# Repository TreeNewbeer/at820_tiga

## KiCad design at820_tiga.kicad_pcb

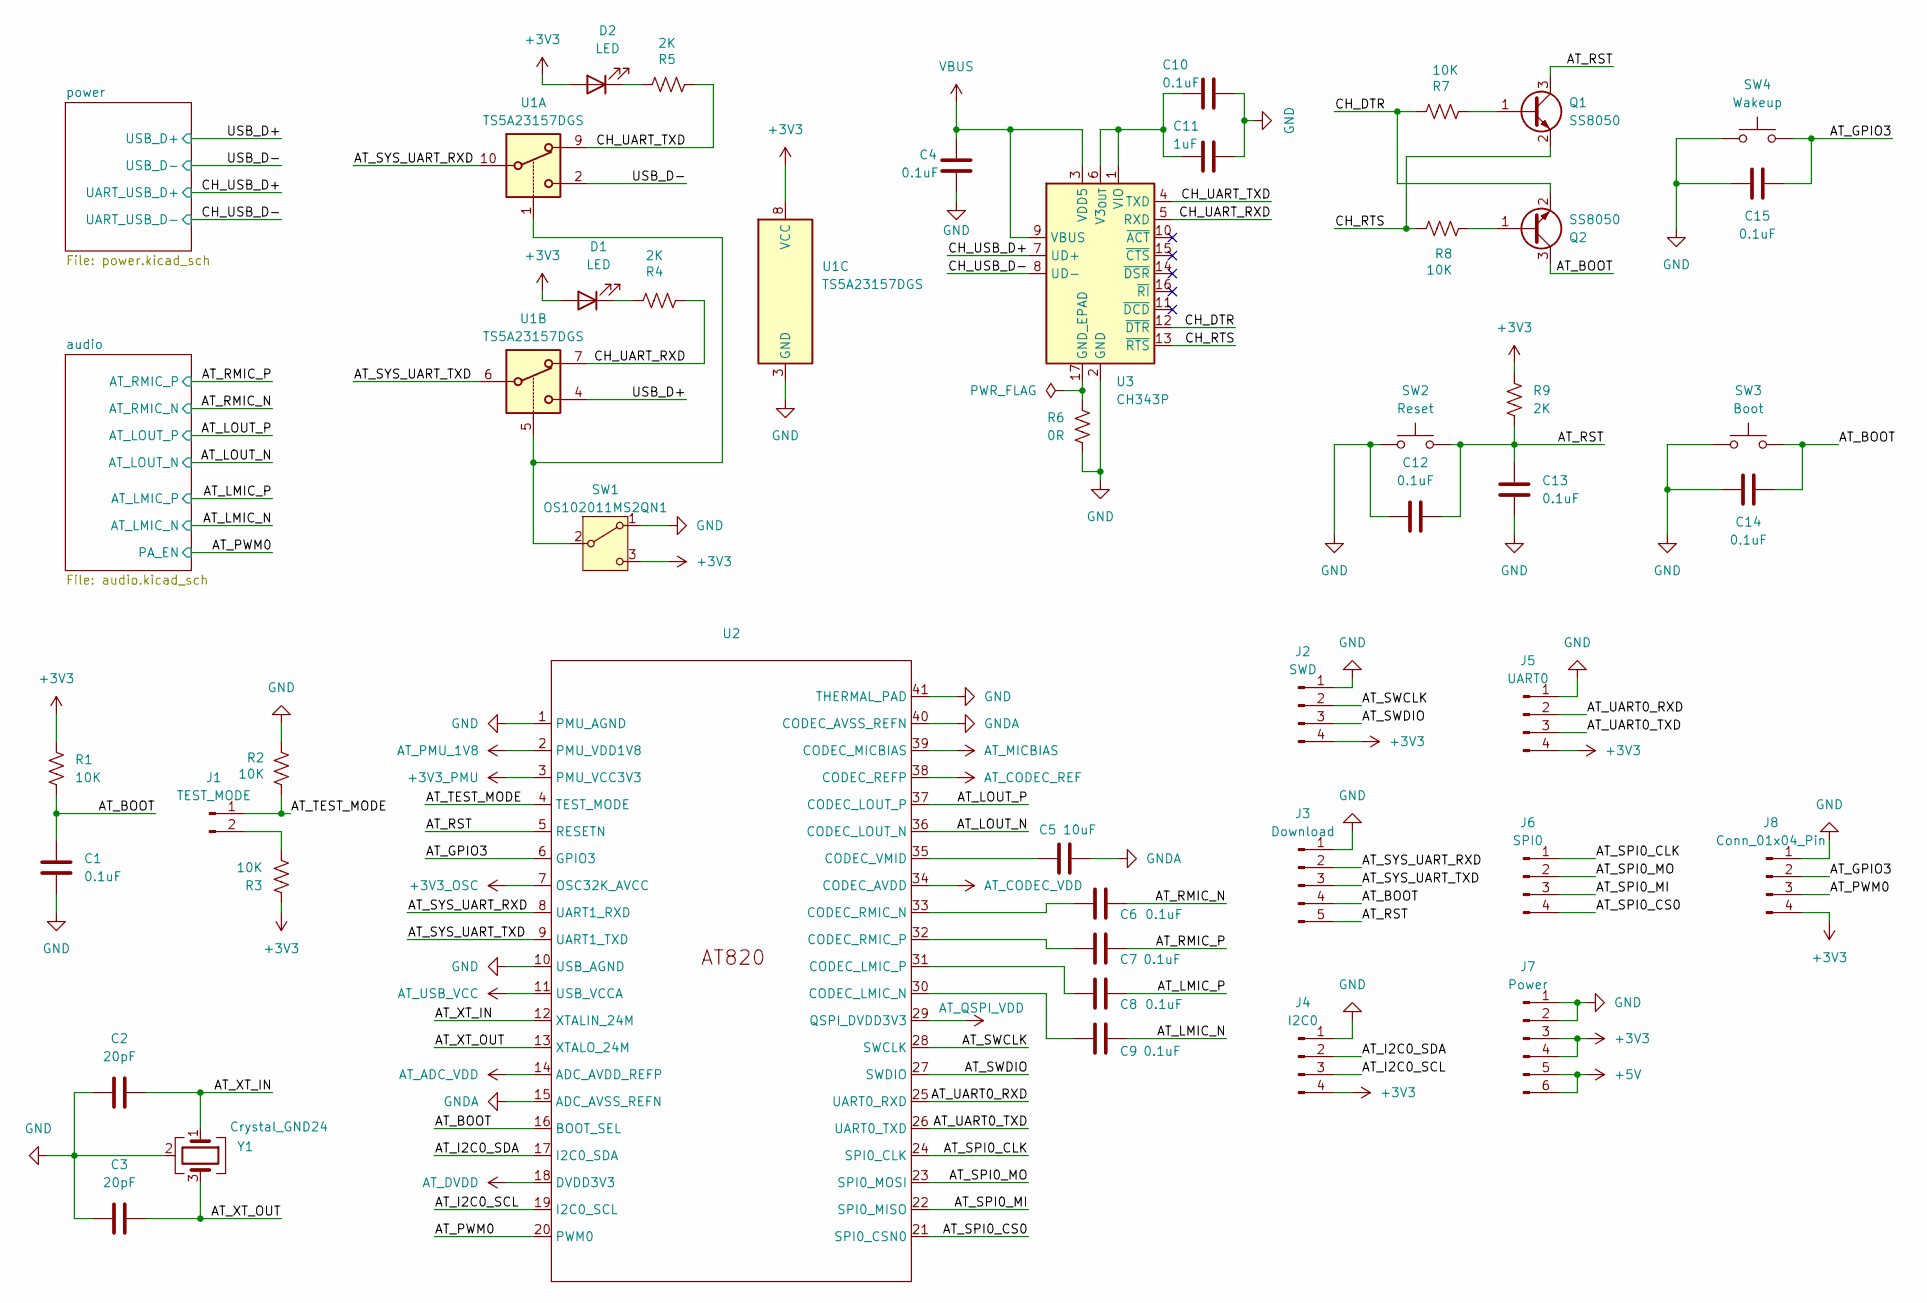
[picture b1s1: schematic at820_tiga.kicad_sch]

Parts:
C1, C4, C6, C7, C8, C9, C10, C12, C13, C14, C15: 0.1uF; C_0603_1608Metric_Pad1.08x0.95mm_HandSolder
C2, C3: 20pF; C_0603_1608Metric_Pad1.08x0.95mm_HandSolder
C5: 10uF; C_0603_1608Metric_Pad1.08x0.95mm_HandSolder
C11: 1uF; C_0603_1608Metric_Pad1.08x0.95mm_HandSolder
D1, D2: LED; LED_0603_1608Metric_Pad1.05x0.95mm_HandSolder
J1: TEST_MODE; PinHeader_1x02_P2.54mm_Vertical
J2: SWD; PinHeader_1x04_P2.54mm_Vertical
J3: Download; PinHeader_1x05_P2.54mm_Vertical
J4: I2C0; PinHeader_1x04_P2.54mm_Vertical
J5: UART0; PinHeader_1x04_P2.54mm_Vertical
J6: SPI0; PinHeader_1x04_P2.54mm_Vertical
J7: Power; PinHeader_1x06_P2.54mm_Vertical
J8: Conn_01x04_Pin; PinHeader_1x04_P2.54mm_Vertical
Q1, Q2: SS8050; SOT-23
R1, R2, R3, R7, R8: 10K; R_0603_1608Metric_Pad0.98x0.95mm_HandSolder
R4, R5, R9: 2K; R_0603_1608Metric_Pad0.98x0.95mm_HandSolder
R6: 0R; R_0603_1608Metric_Pad0.98x0.95mm_HandSolder
SW1: OS102011MS2QN1; SW_Slide_SPDT_Straight_CK_OS102011MS2Q
SW2: Reset; SW_SPST_PTS810
SW3: Boot; SW_SPST_PTS810
SW4: Wakeup; SW_SPST_PTS810
U1: TS5A23157DGS; TSSOP-10_3x3mm_P0.5mm
U2: QFN-40-1EP_5x5mm_P0.4mm_EP3.6x3.6mm
U3: CH343P; WCH_QFN-16-1EP_3x3mm_P0.5mm_EP1.8x1.8mm
Y1: Crystal_GND24; Crystal_SMD_3225-4Pin_3.2x2.5mm

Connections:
+3V3: D1.2 (A), D2.2 (A), J2.4, J4.4, J5.4, J7.3, J7.4, J8.4, R1.1, R3.1, R9.1, SW1.3 (C), U1.8 (VCC), U2.3 (PMU_VCC3V3), U2.7 (OSC32K_AVCC), U2.11 (USB_VCCA), U2.14 (ADC_AVDD_REFP), U2.18 (DVDD3V3), U2.34 (CODEC_AVDD); also elsewhere on the board
+5V: J7.5, J7.6; also elsewhere on the board
/AT_BOOT: C1.1, C14.2, J3.4, Q2.3 (C), R1.2, SW3.2, U2.16 (BOOT_SEL)
/AT_GPIO3: C15.2, J8.2, SW4.2, U2.6 (GPIO3)
/AT_I2C0_SCL: J4.3, U2.19 (I2C0_SCL)
/AT_I2C0_SDA: J4.2, U2.17 (I2C0_SDA)
/AT_LMIC_N: C9.1; also elsewhere on the board
/AT_LMIC_P: C8.1; also elsewhere on the board
/AT_LOUT_N: U2.36 (CODEC_LOUT_N); also elsewhere on the board
/AT_LOUT_P: U2.37 (CODEC_LOUT_P); also elsewhere on the board
/AT_PWM0: J8.3, U2.20 (PWM0); also elsewhere on the board
/AT_RMIC_N: C6.1; also elsewhere on the board
/AT_RMIC_P: C7.1; also elsewhere on the board
/AT_RST: C12.2, C13.1, J3.5, Q1.3 (C), R9.2, SW2.2, U2.5 (RESETN)
/AT_SPI0_CLK: J6.1, U2.24 (SPI0_CLK)
/AT_SPI0_CS0: J6.4, U2.21 (SPI0_CSN0)
/AT_SPI0_MI: J6.3, U2.22 (SPI0_MISO)
/AT_SPI0_MO: J6.2, U2.23 (SPI0_MOSI)
/AT_SWCLK: J2.2, U2.28 (SWCLK)
/AT_SWDIO: J2.3, U2.27 (SWDIO)
/AT_SYS_UART_RXD: J3.2, U1.10, U2.8 (UART1_RXD)
/AT_SYS_UART_TXD: J3.3, U1.6, U2.9 (UART1_TXD)
/AT_TEST_MODE: J1.1, R2.1, U2.4 (TEST_MODE)
/AT_UART0_RXD: J5.2, U2.25 (UART0_RXD)
/AT_UART0_TXD: J5.3, U2.26 (UART0_TXD)
/AT_XT_IN: C2.1, U2.12 (XTALIN_24M), Y1.1
/AT_XT_OUT: C3.1, U2.13 (XTALO_24M), Y1.3
/CH_DTR: Q2.2 (E), R7.2, U3.12 (~DTR)
/CH_RTS: Q1.2 (E), R8.1, U3.13 (~RTS)
/CH_UART_RXD: R4.1, U1.7, U3.5 (RXD)
/CH_UART_TXD: R5.1, U1.9, U3.4 (TXD)
/CH_USB_D+: U3.7 (UD+); also elsewhere on the board
/CH_USB_D-: U3.8 (UD-); also elsewhere on the board
/USB_D+: U1.4; also elsewhere on the board
/USB_D-: U1.2; also elsewhere on the board
AT_CODEC_REF: U2.38 (CODEC_REFP); also elsewhere on the board
AT_MICBIAS: U2.39 (CODEC_MICBIAS); also elsewhere on the board
AT_PMU_1V8: U2.2 (PMU_VDD1V8); also elsewhere on the board
AT_QSPI_VDD: U2.29 (QSPI_DVDD3V3); also elsewhere on the board
GND: C1.2, C2.2, C3.2, C4.2, C10.2, C11.2, C12.1, C13.2, C14.1, C15.1, J2.1, J3.1, J4.1, J5.1, J7.1, J7.2, J8.1, R2.2, R6.1, SW1.1 (A), SW2.1, SW3.1, SW4.1, U1.3 (GND), U2.1 (PMU_AGND), U2.10 (USB_AGND), U2.41 (THERMAL_PAD), U3.2 (GND), Y1.2 (G), Y1.4 (G); also elsewhere on the board
GNDA: C5.1, U2.15 (ADC_AVSS_REFN), U2.40 (CODEC_AVSS_REFN); also elsewhere on the board
unnamed: D1.1 (K), R4.2
unnamed: D2.1 (K), R5.2
unnamed: J1.2, R3.2
unnamed: Q1.1 (B), R7.1
unnamed: Q2.1 (B), R8.2
unnamed: SW1.2 (B), U1.1, U1.5
unnamed: C9.2, U2.30 (CODEC_LMIC_N)
unnamed: C8.2, U2.31 (CODEC_LMIC_P)
unnamed: C6.2, U2.33 (CODEC_RMIC_N)
unnamed: C7.2, U2.32 (CODEC_RMIC_P)
unnamed: C5.2, U2.35 (CODEC_VMID)
unnamed: R6.2, U3.17 (GND_EPAD)
unnamed: C10.1, C11.1, U3.1 (VIO), U3.6 (V3_{OUT})
VBUS: C4.1, U3.3 (VDD5), U3.9 (VBUS); also elsewhere on the board

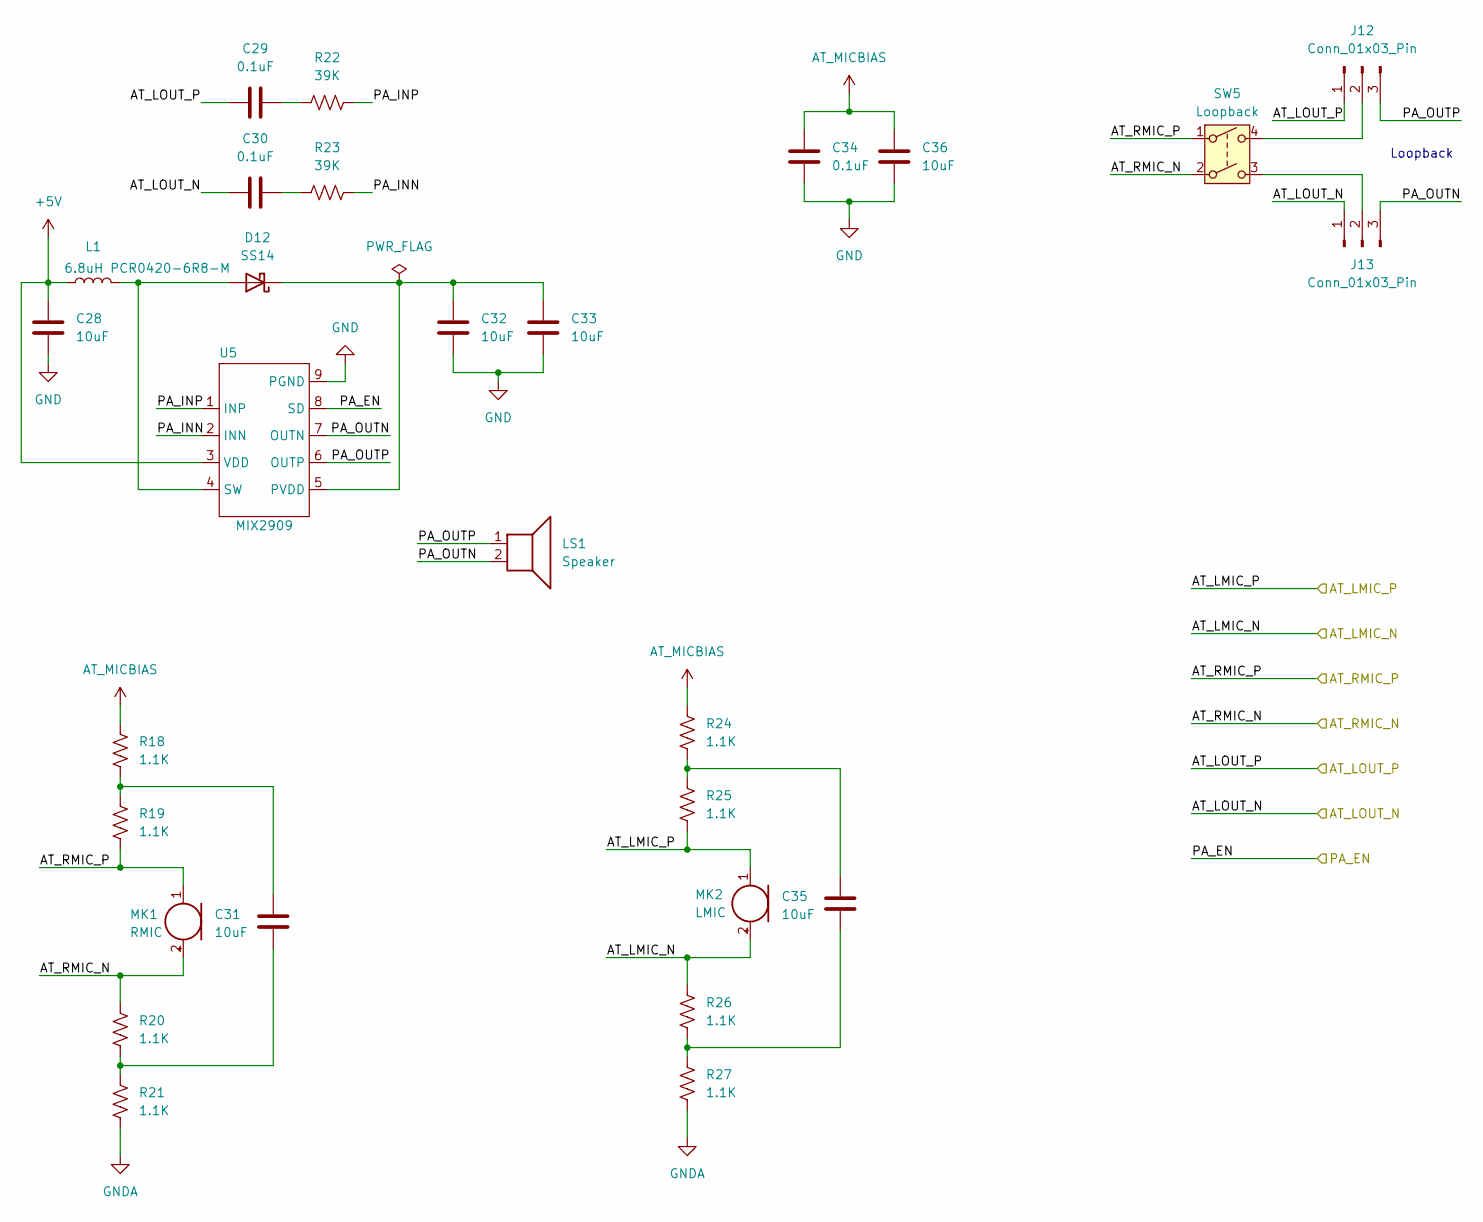
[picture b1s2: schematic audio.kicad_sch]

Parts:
C28, C31, C32, C33, C35, C36: 10uF; C_0603_1608Metric_Pad1.08x0.95mm_HandSolder
C29, C30, C34: 0.1uF; C_0603_1608Metric_Pad1.08x0.95mm_HandSolder
D12: SS14; D_SMA_Handsoldering
J12, J13: Conn_01x03_Pin; PinHeader_1x03_P2.54mm_Vertical
L1: 6.8uH PCR0420-6R8-M; L_APV_APH0420
LS1: Speaker; Molex_PicoBlade_53047-0210_1x02_P1.25mm_Vertical
MK1: RMIC; POM-2244P-C3310-2-R
MK2: LMIC; POM-2244P-C3310-2-R
R18, R19, R20, R21, R24, R25, R26, R27: 1.1K; R_0603_1608Metric_Pad0.98x0.95mm_HandSolder
R22, R23: 39K; R_0603_1608Metric_Pad0.98x0.95mm_HandSolder
SW5: Loopback; SW_DIP_SPSTx02_Slide_Copal_CHS-02B_W7.62mm_P1.27mm
U5: MIX2909; SOIC-8-1EP_3.9x4.9mm_P1.27mm_EP2.29x3mm

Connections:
+5V: C28.1, L1.1, U5.3 (VDD); also elsewhere on the board
/AT_LMIC_N: MK2.2 (+), R26.1; also elsewhere on the board
/AT_LMIC_P: MK2.1 (-), R25.2; also elsewhere on the board
/AT_LOUT_N: C30.1, J13.1; also elsewhere on the board
/AT_LOUT_P: C29.1, J12.1; also elsewhere on the board
/AT_PWM0: U5.8 (SD); also elsewhere on the board
/AT_RMIC_N: MK1.2 (+), R20.1, SW5.2; also elsewhere on the board
/AT_RMIC_P: MK1.1 (-), R19.2, SW5.1; also elsewhere on the board
/audio/PA_INN: R23.2, U5.2 (INN)
/audio/PA_INP: R22.2, U5.1 (INP)
/audio/PA_OUTN: J13.3, LS1.2, U5.7 (OUTN)
/audio/PA_OUTP: J12.3, LS1.1, U5.6 (OUTP)
AT_MICBIAS: C34.1, C36.1, R18.1, R24.1; also elsewhere on the board
GND: C28.2, C32.2, C33.2, C34.2, C36.2, U5.9 (PGND); also elsewhere on the board
GNDA: R21.2, R27.2; also elsewhere on the board
unnamed: C29.2, R22.1
unnamed: C30.2, R23.1
unnamed: C31.1, R20.2, R21.1
unnamed: C31.2, R18.2, R19.1
unnamed: C35.1, R26.2, R27.1
unnamed: C35.2, R24.2, R25.1
unnamed: D12.2 (A), L1.2, U5.4 (SW)
unnamed: C32.1, C33.1, D12.1 (K), U5.5 (PVDD)
unnamed: J12.2, SW5.4
unnamed: J13.2, SW5.3

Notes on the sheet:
Loopback

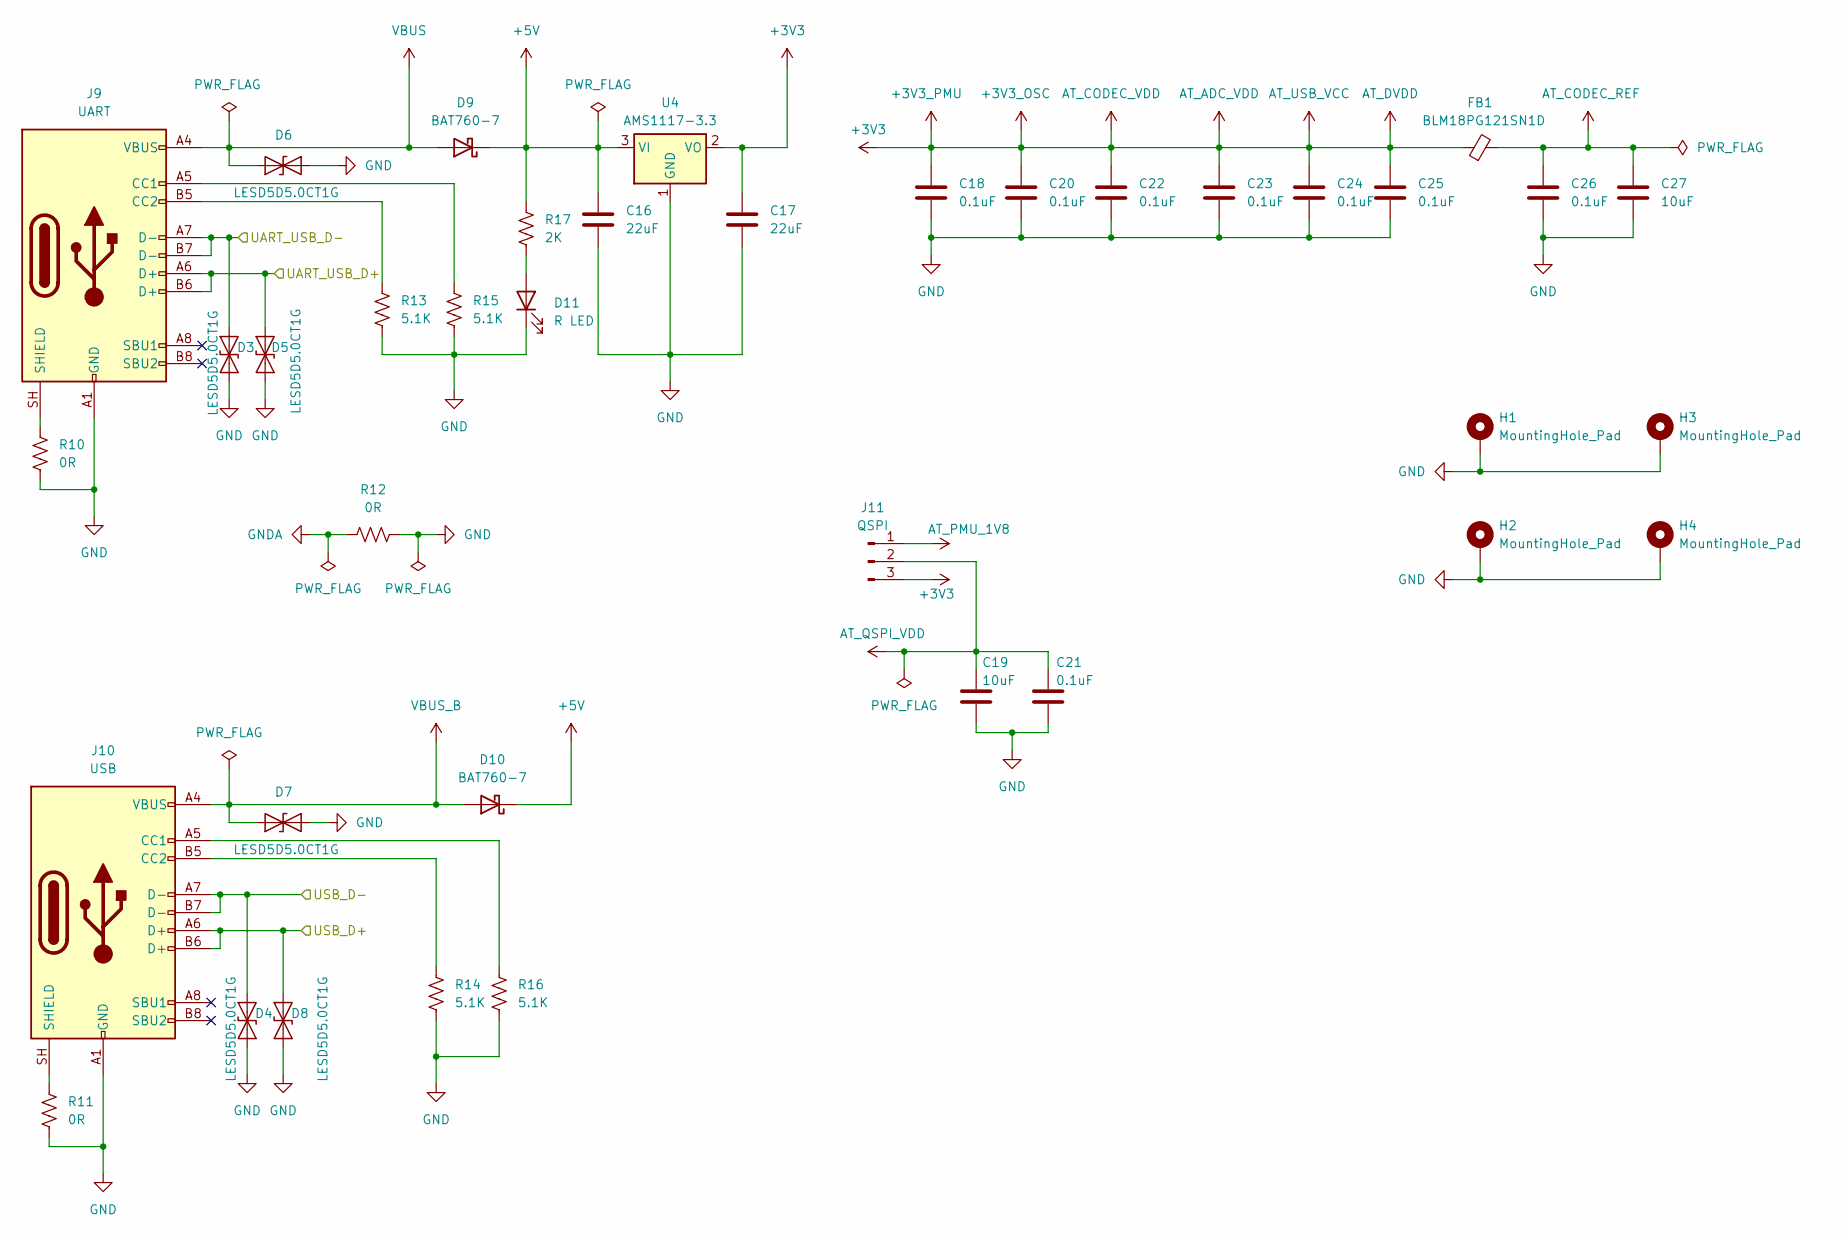
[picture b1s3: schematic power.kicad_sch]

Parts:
C16, C17: 22uF; C_0603_1608Metric_Pad1.08x0.95mm_HandSolder
C18, C20, C21, C22, C23, C24, C25, C26: 0.1uF; C_0603_1608Metric_Pad1.08x0.95mm_HandSolder
C19, C27: 10uF; C_0603_1608Metric_Pad1.08x0.95mm_HandSolder
D3, D4, D5, D6, D7, D8: LESD5D5.0CT1G; D_SOD-523
D9, D10: BAT760-7; D_SOD-323
D11: R LED; LED_0603_1608Metric_Pad1.05x0.95mm_HandSolder
FB1: BLM18PG121SN1D; L_0603_1608Metric_Pad1.05x0.95mm_HandSolder
H1, H2, H3, H4: MountingHole_Pad; MountingHole_3.2mm_M3_Pad
J9: UART; USB_C_Receptacle_GCT_USB4105-xx-A_16P_TopMnt_Horizontal
J10: USB; USB_C_Receptacle_GCT_USB4105-xx-A_16P_TopMnt_Horizontal
J11: QSPI; PinHeader_1x03_P2.54mm_Vertical
R10, R11, R12: 0R; R_0603_1608Metric_Pad0.98x0.95mm_HandSolder
R13, R14, R15, R16: 5.1K; R_0603_1608Metric_Pad0.98x0.95mm_HandSolder
R17: 2K; R_0603_1608Metric_Pad0.98x0.95mm_HandSolder
U4: AMS1117-3.3; SOT-223-3_TabPin2

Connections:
+3V3: C17.1, C18.1, C20.1, C22.1, C23.1, C24.1, C25.1, FB1.1, J11.3, U4.2 (VO); also elsewhere on the board
+5V: C16.1, D9.1 (K), D10.1 (K), R17.1, U4.3 (VI); also elsewhere on the board
/CH_USB_D+: D5.2 (A2), J9.A6 (D+), J9.B6 (D+); also elsewhere on the board
/CH_USB_D-: D3.2 (A2), J9.A7 (D-), J9.B7 (D-); also elsewhere on the board
/USB_D+: D8.2 (A2), J10.A6 (D+), J10.B6 (D+); also elsewhere on the board
/USB_D-: D4.2 (A2), J10.A7 (D-), J10.B7 (D-); also elsewhere on the board
AT_CODEC_REF: C26.1, C27.1, FB1.2; also elsewhere on the board
AT_PMU_1V8: J11.1; also elsewhere on the board
AT_QSPI_VDD: C19.1, C21.1, J11.2; also elsewhere on the board
GND: C16.2, C17.2, C18.2, C19.2, C20.2, C21.2, C22.2, C23.2, C24.2, C25.2, C26.2, C27.2, D3.1 (A1), D4.1 (A1), D5.1 (A1), D6.1 (A1), D7.1 (A1), D8.1 (A1), D11.1 (K), H1.1 (1_1), H2.1 (1_1), H3.1 (1_1), H4.1 (1_1), J9.A1 (GND), J9.A12 (GND), J9.B1 (GND), J9.B12 (GND), J10.A1 (GND), J10.A12 (GND), J10.B1 (GND), J10.B12 (GND), R10.1, R11.1, R12.2, R13.2, R14.2, R15.2, R16.2, U4.1 (GND); also elsewhere on the board
GNDA: R12.1; also elsewhere on the board
unnamed: D11.2 (A), R17.2
unnamed: J9.A5 (CC1), R15.1
unnamed: J9.B5 (CC2), R13.1
unnamed: J9.SH (SHIELD), R10.2
unnamed: J10.A5 (CC1), R16.1
unnamed: J10.B5 (CC2), R14.1
unnamed: J10.SH (SHIELD), R11.2
VBUS: D6.2 (A2), D9.2 (A), J9.A4 (VBUS), J9.A9 (VBUS), J9.B4 (VBUS), J9.B9 (VBUS); also elsewhere on the board
VBUS_B: D7.2 (A2), D10.2 (A), J10.A4 (VBUS), J10.A9 (VBUS), J10.B4 (VBUS), J10.B9 (VBUS)

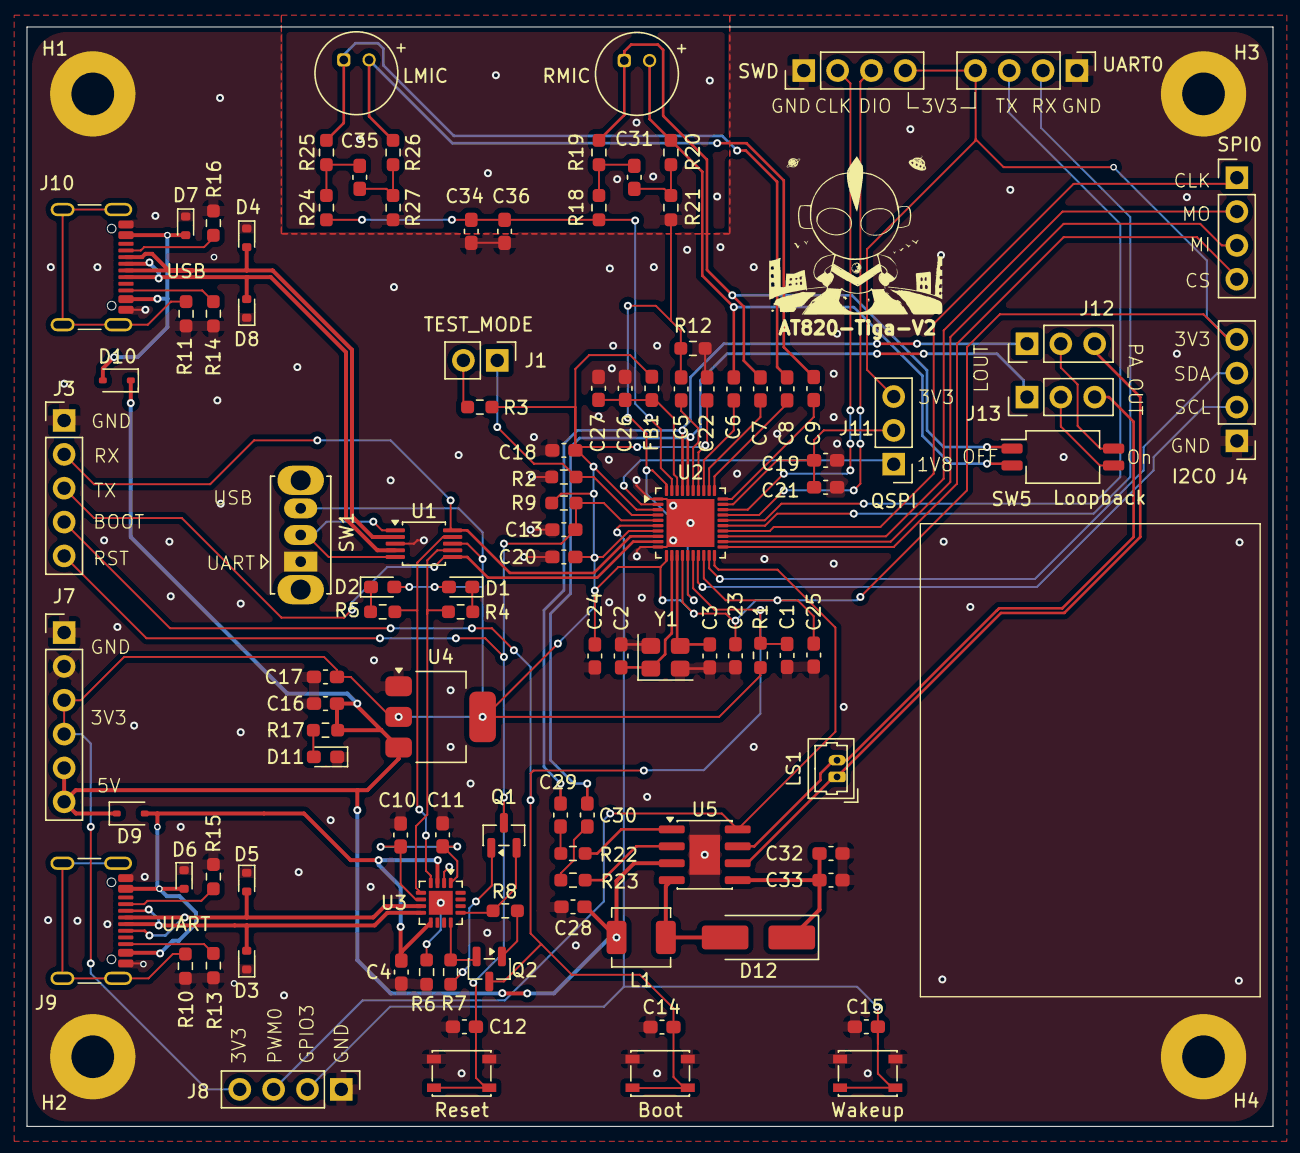
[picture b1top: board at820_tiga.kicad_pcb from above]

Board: 2 copper layers, 93.5 x 82.5 mm, 111 parts (0 on the bottom side), 77 nets.

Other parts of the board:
AT820-Tiga-V2: LOGO; logo

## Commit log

2026-05-23 at820 tiga, first init
2026-05-24 add claude files
2026-05-24 modify board egde
2026-05-25 pcb dev
2026-05-27 beta 2, modify board size, add some silkscreen
2026-05-28 refactor crystal pcb
2026-05-28 add logo, fix all no connect bugs
2026-05-28 output gerber for JLC
2026-06-02 fix ch343p bug and other bugs in sch
2026-06-04 v2 done
